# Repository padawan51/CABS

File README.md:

# CABS
Charge abort Bluetooth System

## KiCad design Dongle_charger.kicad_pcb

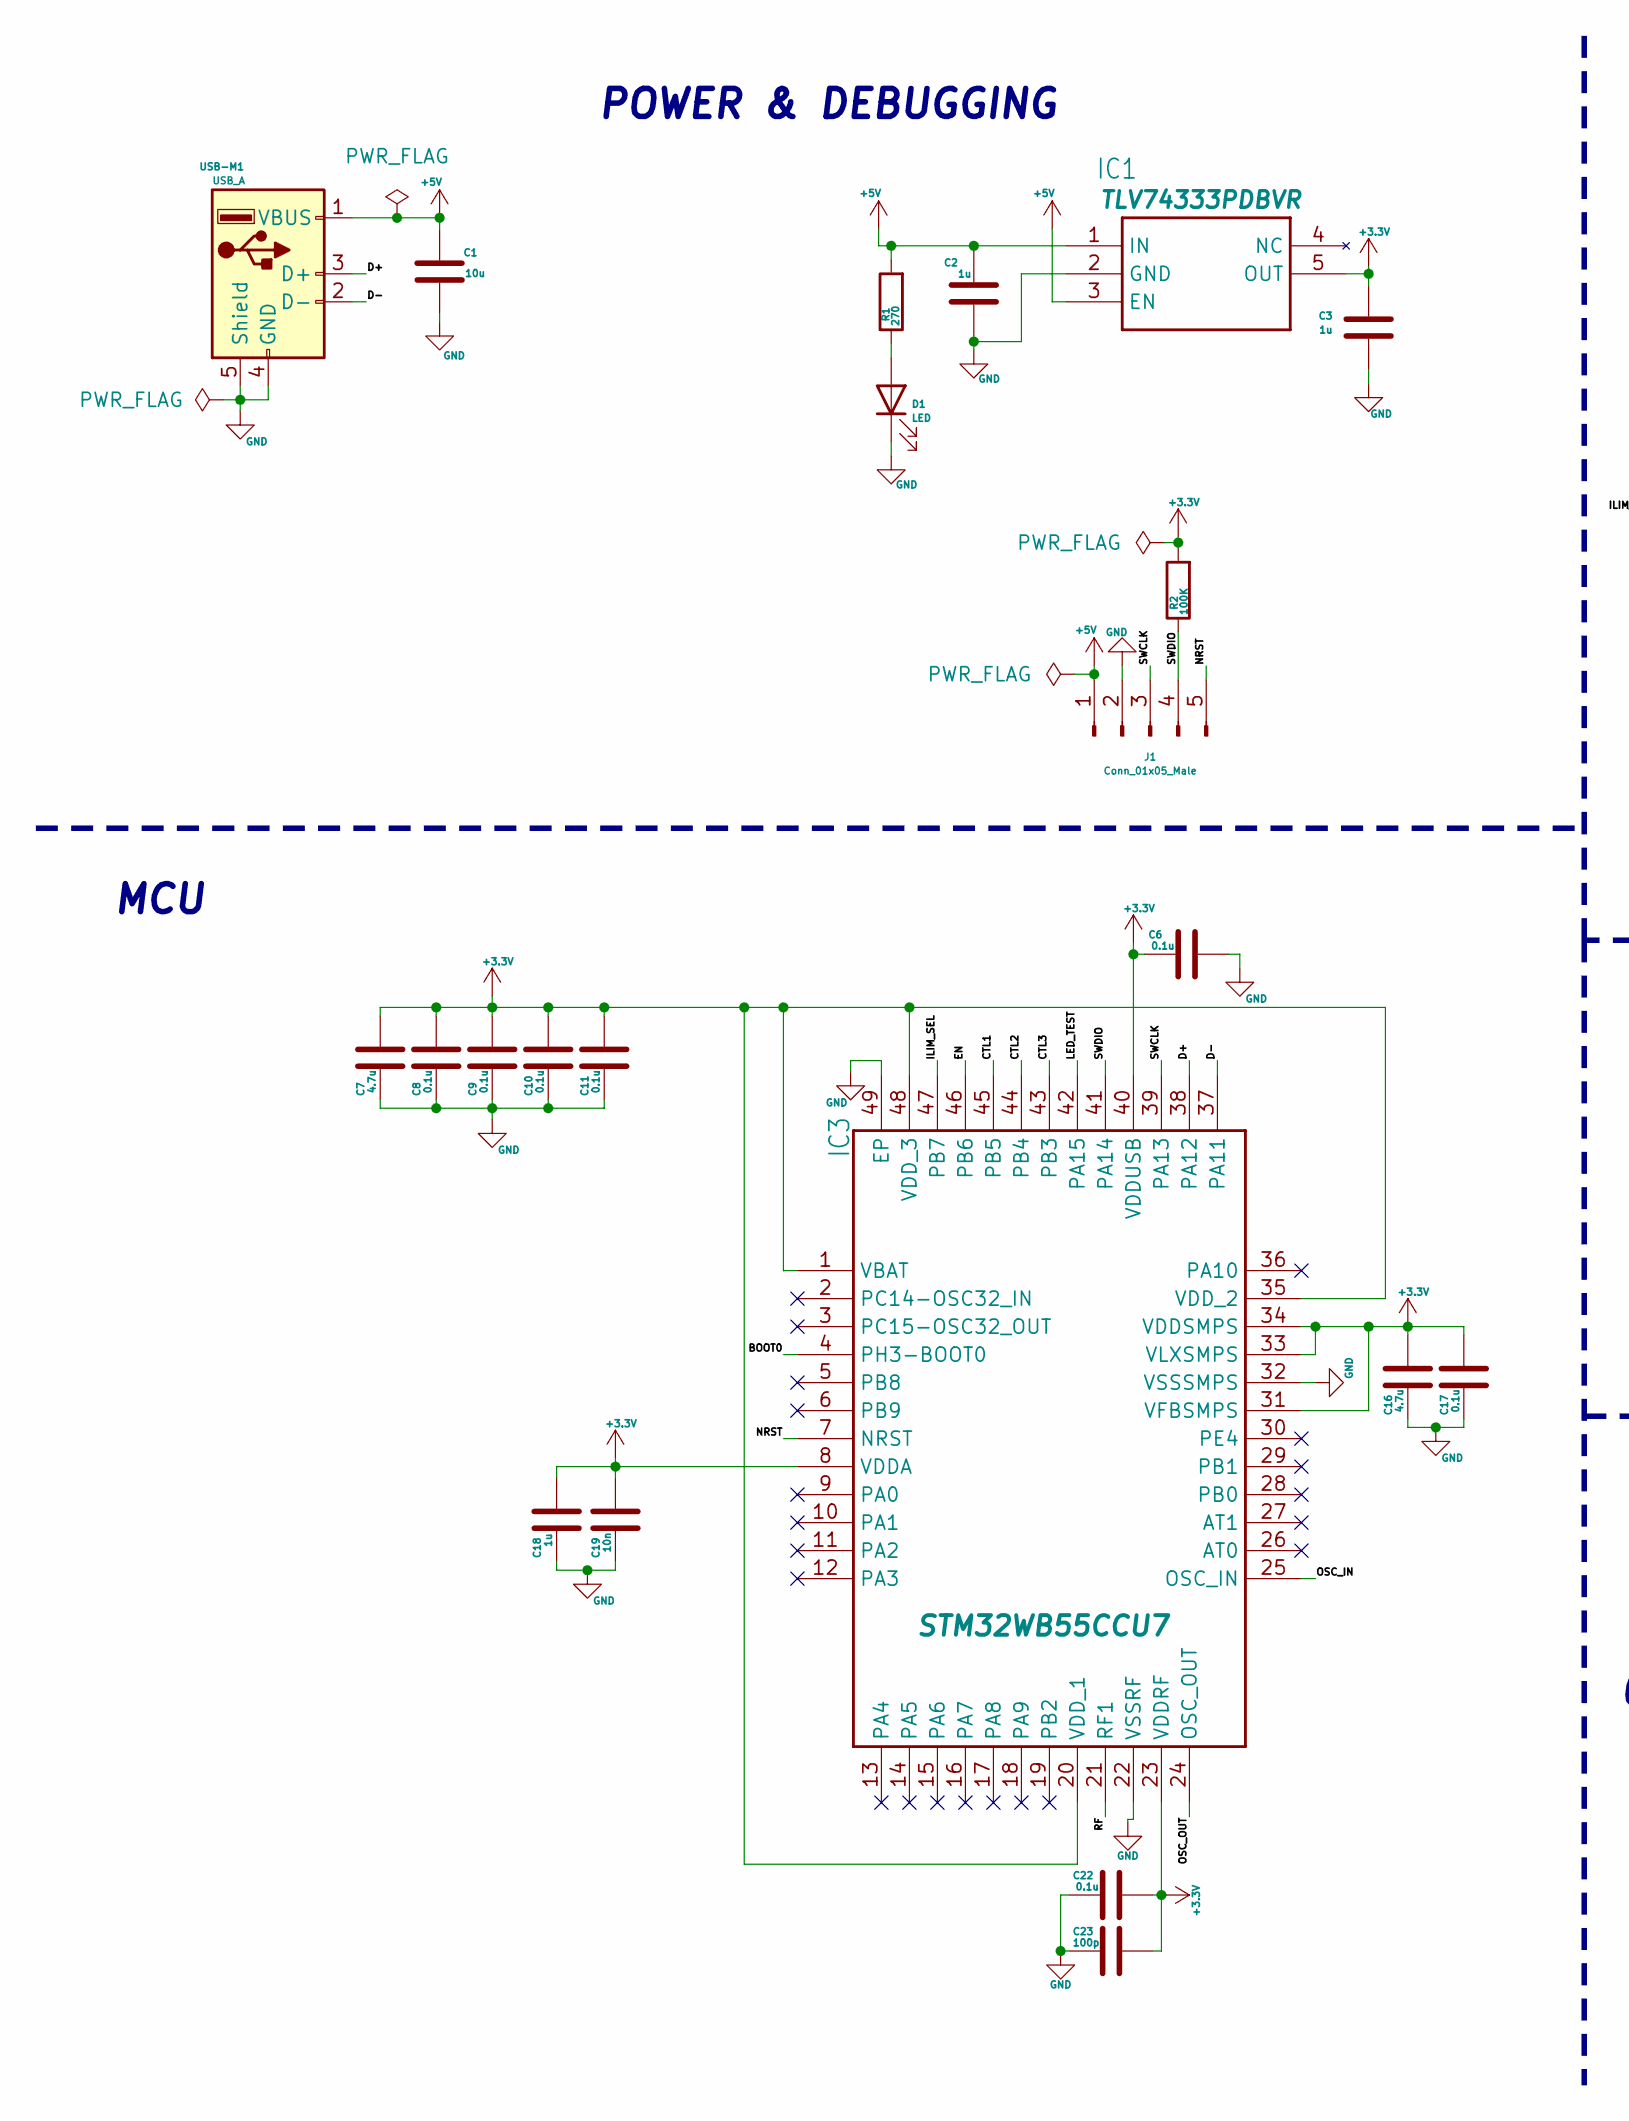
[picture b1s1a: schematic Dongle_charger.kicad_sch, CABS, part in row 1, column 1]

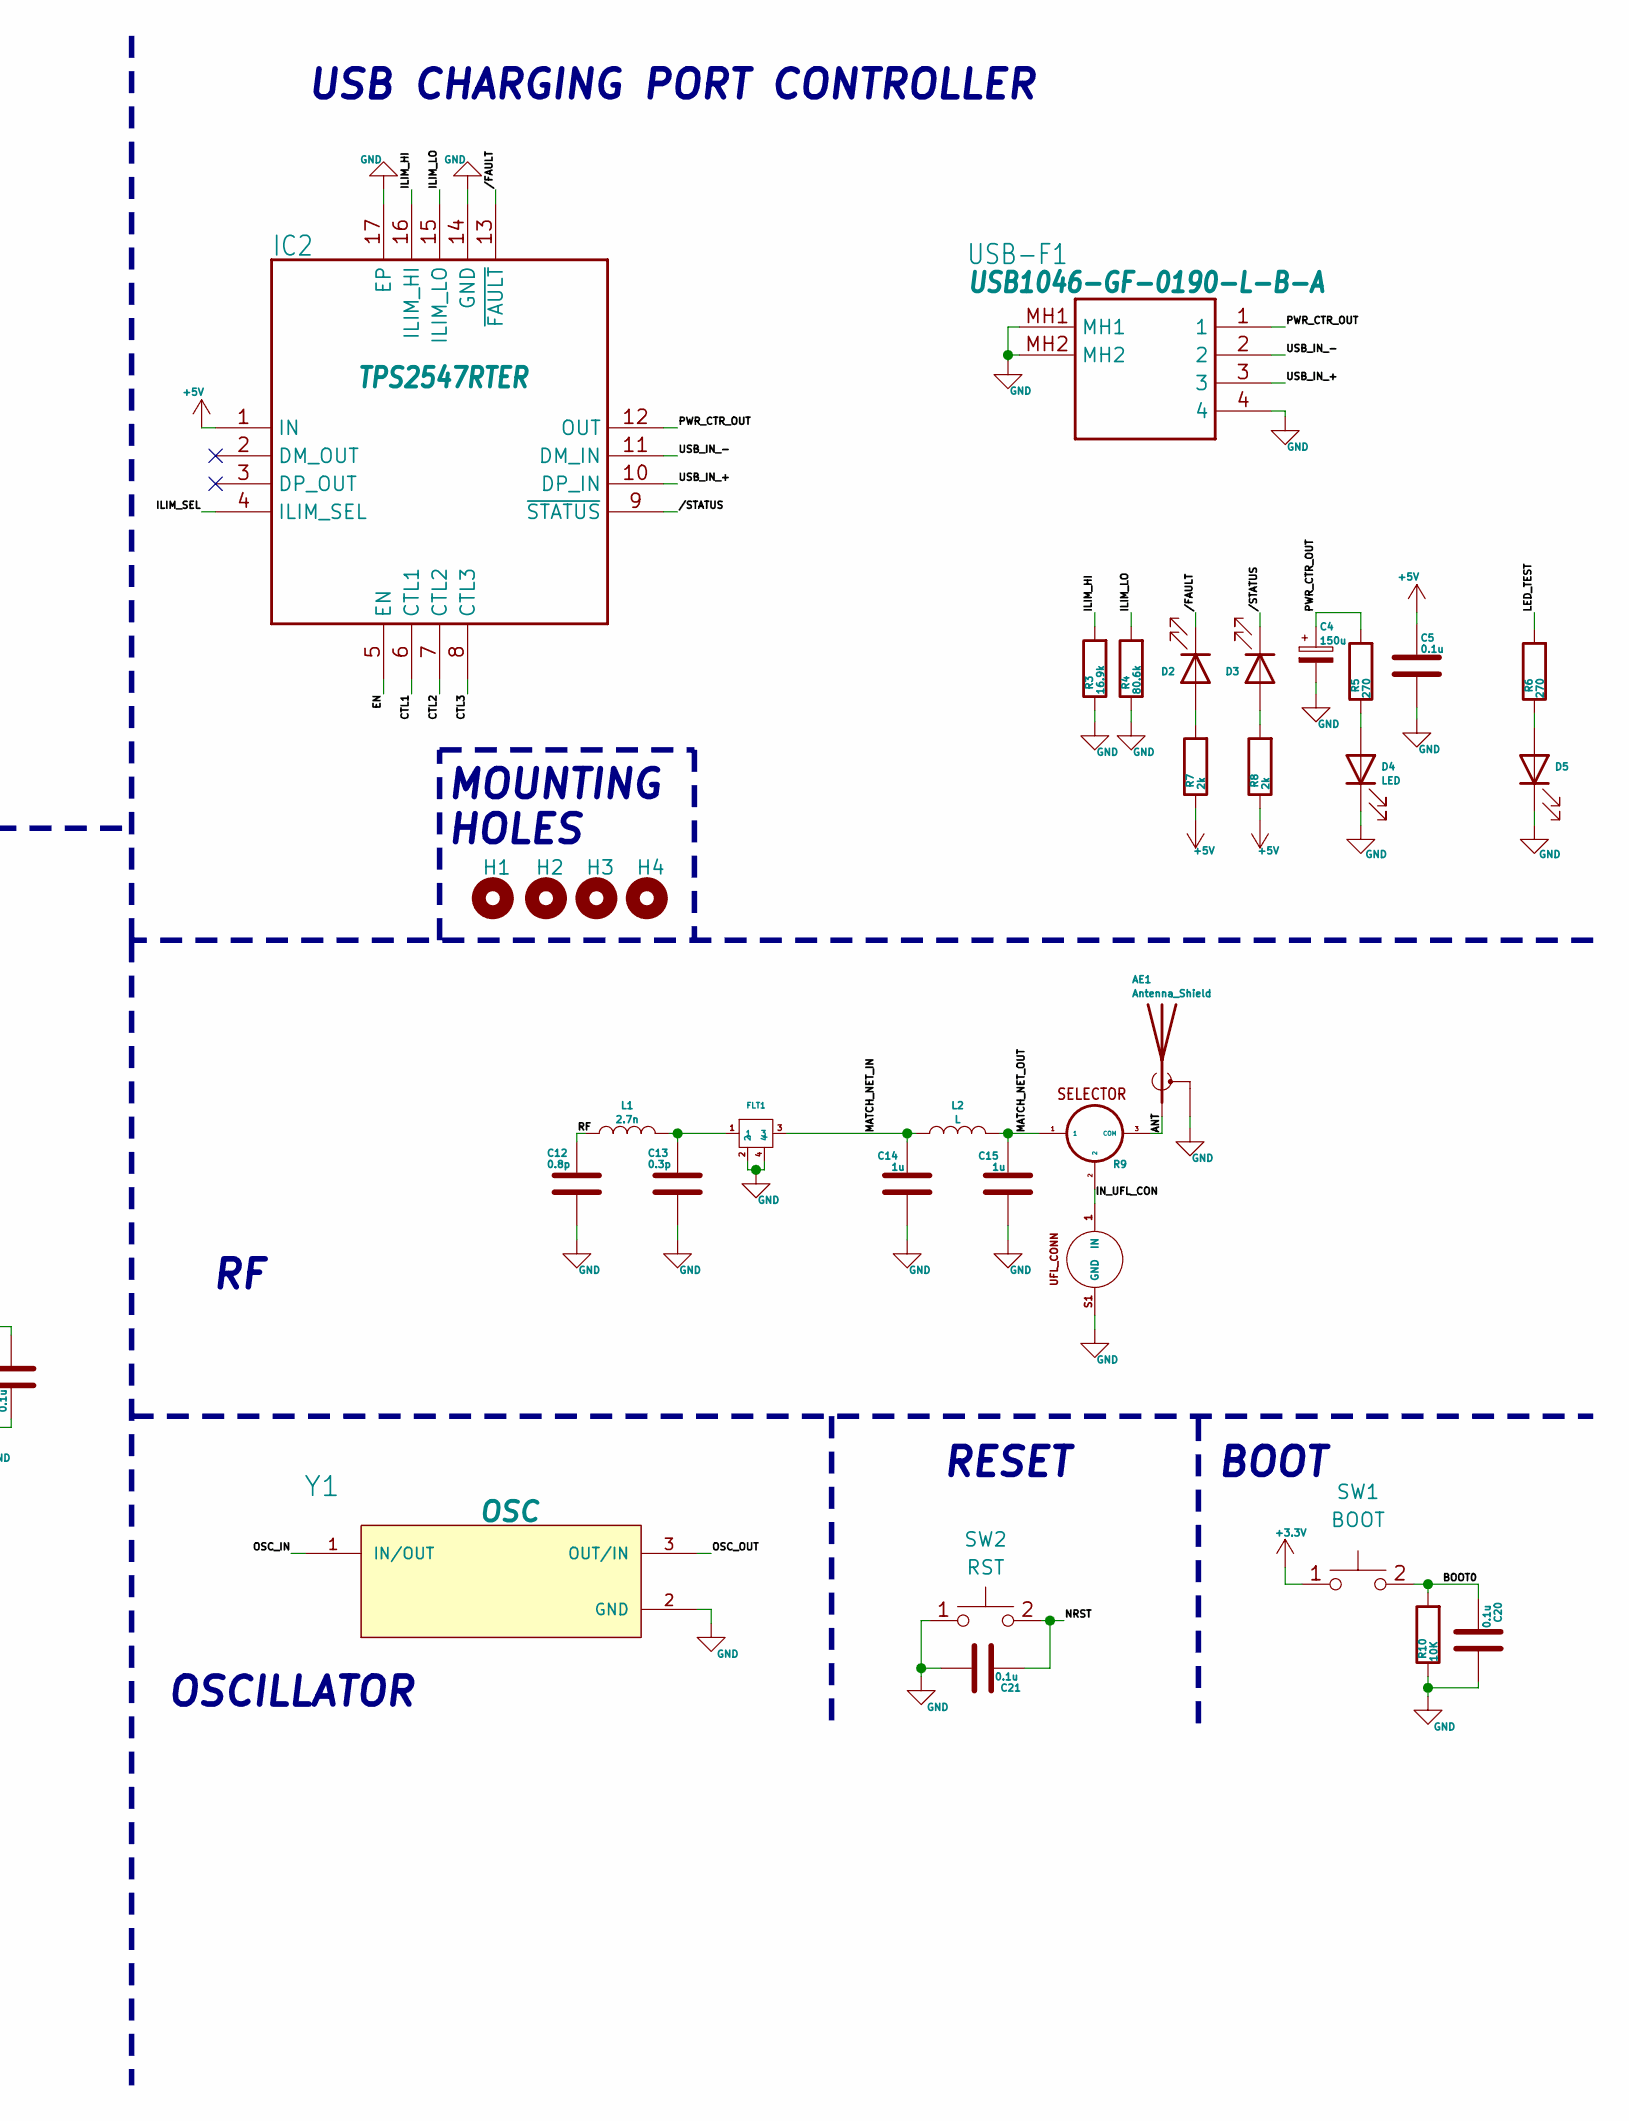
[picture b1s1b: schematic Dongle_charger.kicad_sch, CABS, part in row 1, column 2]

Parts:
AE1: Antenna_Shield; Texas_SWRA117D_2.4GHz_Right
C1: 10u; C_0402_1005Metric
C2, C3, C14, C15, C18: 1u; C_0402_1005Metric
C4: 150u; CAPPM7343X310N
C5, C6, C8, C9, C10, C11, C17, C20, C21, C22: 0.1u; C_0402_1005Metric
C7, C16: 4.7u; C_0402_1005Metric
C12: 0.8p; C_0402_1005Metric
C13: 0.3p; C_0402_1005Metric
C19: 10n; C_0402_1005Metric
C23: 100p; C_0402_1005Metric
D1, D4: LED; LEDC1608X80N
D2: fault; LEDC1608X80N
D3: status; LEDC1608X80N
D5: TEST; LEDC1608X80N
FLT1: DLF162500LT-5028A1; DEA160915LT-1169
H1, H2, H3, H4: MountingHole; MountingHole_2.7mm_M2.5_ISO14580
IC1: TLV74333PDBVR; SOT95P280X145-5N
IC2: TPS2547RTER; QFN50P300X300X80-17N
IC3: QFN50P700X700X60-49N
J1: Conn_01x05_Male; PinHeader_1x05_P2.54mm_Vertical
L1: 2.7n; L_0402_1005Metric
L2: L; L_0402_1005Metric
R1, R5, R6: 270; R_0402_1005Metric
R2: 100K; R_0402_1005Metric
R3: 16.9k; R_0402_1005Metric
R4: 80.6k; R_0402_1005Metric
R7, R8: 2k; R_0402_1005Metric
R9: 3_PIN_RES; SELECTOR
R10: 10K; R_0402_1005Metric
SW1: BOOT; KXT311LHS
SW2: RST; KXT311LHS
UFL1: UFL_CONNECTOR; LINX_CONMHF1-SMD-G-T
USB-F1: USB1046-GF-0190-L-B-A; GCT_USB1046-XX-XXXX-X-B-X_REVB
USB-M1: USB_A; GCT_USB1061-XX-X-X_REVA
Y1: OSC; XTAL_ECS-320-8-37-CKM-TR3; PARTREV 2017

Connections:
+3.3V: C3.1, C6.1, C7.2, C8.2, C9.2, C10.2, C11.2, C16.2, C17.2, C18.2, C19.2, C22.2, C23.2, IC1.5 (OUT), IC3.1 (VBAT), IC3.8 (VDDA), IC3.20 (VDD_1), IC3.23 (VDDRF), IC3.31 (VFBSMPS), IC3.33 (VLXSMPS), IC3.34 (VDDSMPS), IC3.35 (VDD_2), IC3.40 (VDDUSB), IC3.48 (VDD_3), R2.2, SW1.1
+5V: C1.1, C2.1, C5.1, IC1.1 (IN), IC1.3 (EN), IC2.1 (IN), J1.1, R1.2, R7.1, R8.1, USB-M1.1 (VBUS)
/ANT: AE1.1 (A), R9.3 (COM)
/BOOT0: C20.1, IC3.4 (PH3-BOOT0), R10.2, SW1.2
/CTL1: IC2.6 (CTL1), IC3.45 (PB5)
/CTL2: IC2.7 (CTL2), IC3.44 (PB4)
/CTL3: IC2.8 (CTL3), IC3.43 (PB3)
/D+: IC3.38 (PA12), USB-M1.3 (D+)
/D-: IC3.37 (PA11), USB-M1.2 (D-)
/EN: IC2.5 (EN), IC3.46 (PB6)
/ILIM_HI: IC2.16 (ILIM_HI), R3.2
/ILIM_LO: IC2.15 (ILIM_LO), R4.2
/ILIM_SEL: IC2.4 (ILIM_SEL), IC3.47 (PB7)
/IN_UFL_CON: R9.2, UFL1.1 (IN)
/LED_TEST: IC3.42 (PA15), R6.2
/MATCH_NET_IN: C14.1, FLT1.3, L2.1
/MATCH_NET_OUT: C15.1, L2.2, R9.1
/NRST: C21.1, IC3.7 (NRST), J1.5, SW2.2
/OSC_IN: IC3.25 (OSC_IN), Y1.1 (IN/OUT)
/OSC_OUT: IC3.24 (OSC_OUT), Y1.3 (OUT/IN)
/PWR_CTR_OUT: C4.1, IC2.12 (OUT), R5.2, USB-F1.1
/RF: C12.1, IC3.21 (RF1), L1.1
/SWCLK: IC3.39 (PA13), J1.3
/SWDIO: IC3.41 (PA14), J1.4, R2.1
/USB_IN_+: IC2.10 (DP_IN), USB-F1.3
/USB_IN_-: IC2.11 (DM_IN), USB-F1.2
//FAULT: D2.1 (K), IC2.13 (~FAULT)
//STATUS: D3.1 (K), IC2.9 (~STATUS)
GND: AE1.2 (Shield), C1.2, C2.2, C3.2, C4.2, C5.2, C6.2, C7.1, C8.1, C9.1, C10.1, C11.1, C12.2, C13.2, C14.2, C15.2, C16.1, C17.1, C18.1, C19.1, C20.2, C21.2, C22.1, C23.1, D1.1 (K), D4.1 (K), D5.1 (K), FLT1.2, FLT1.4, IC1.2 (GND), IC2.14 (GND), IC2.17 (EP), IC3.22 (VSSRF), IC3.32 (VSSSMPS), IC3.49 (EP), J1.2, R3.1, R4.1, R10.1, SW2.1, UFL1.S1 (GND), UFL1.S2 (GND), UFL1.S3 (GND), USB-F1.4, USB-F1.MH1, USB-F1.MH2, USB-M1.4 (GND), USB-M1.5 (Shield), USB-M1.6 (Shield), Y1.2 (GND), Y1.4 (GND)
unnamed: C13.1, FLT1.1, L1.2
unnamed: D1.2 (A), R1.1
unnamed: D2.2 (A), R7.2
unnamed: D3.2 (A), R8.2
unnamed: D4.2 (A), R5.1
unnamed: D5.2 (A), R6.1

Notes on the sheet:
OSCILLATOR
MCU
RESET
BOOT
POWER & DEBUGGING
USB CHARGING PORT CONTROLLER
MOUNTING HOLES

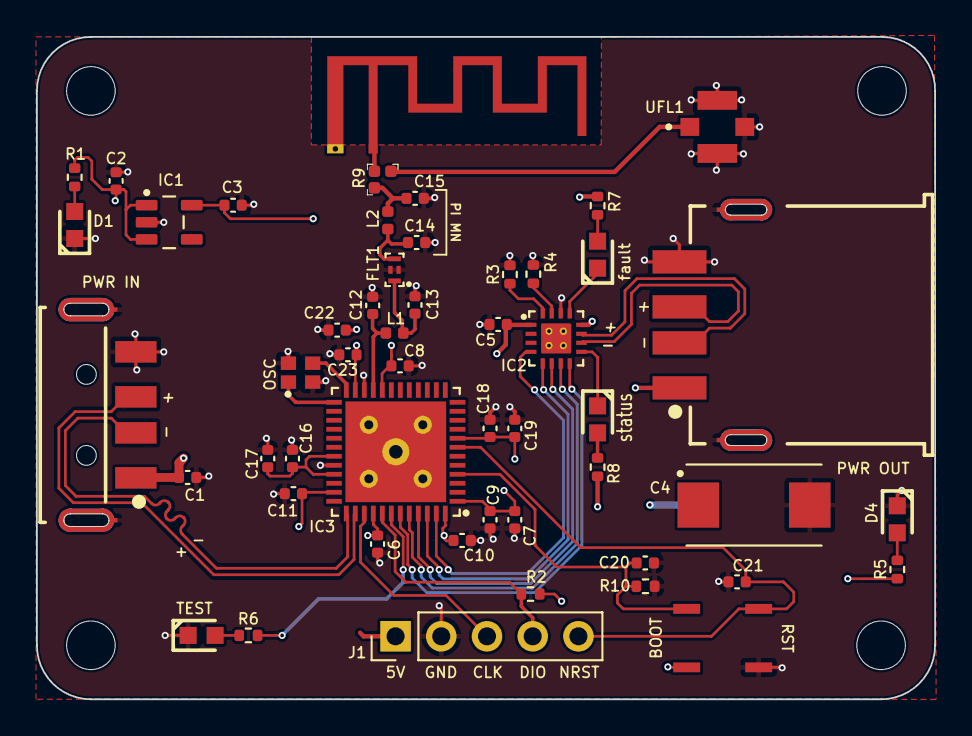
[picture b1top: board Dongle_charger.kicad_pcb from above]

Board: 4 copper layers, 49.9 x 36.8 mm, 56 parts (0 on the bottom side), 35 nets.

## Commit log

2024-09-13 CABS PCB files
